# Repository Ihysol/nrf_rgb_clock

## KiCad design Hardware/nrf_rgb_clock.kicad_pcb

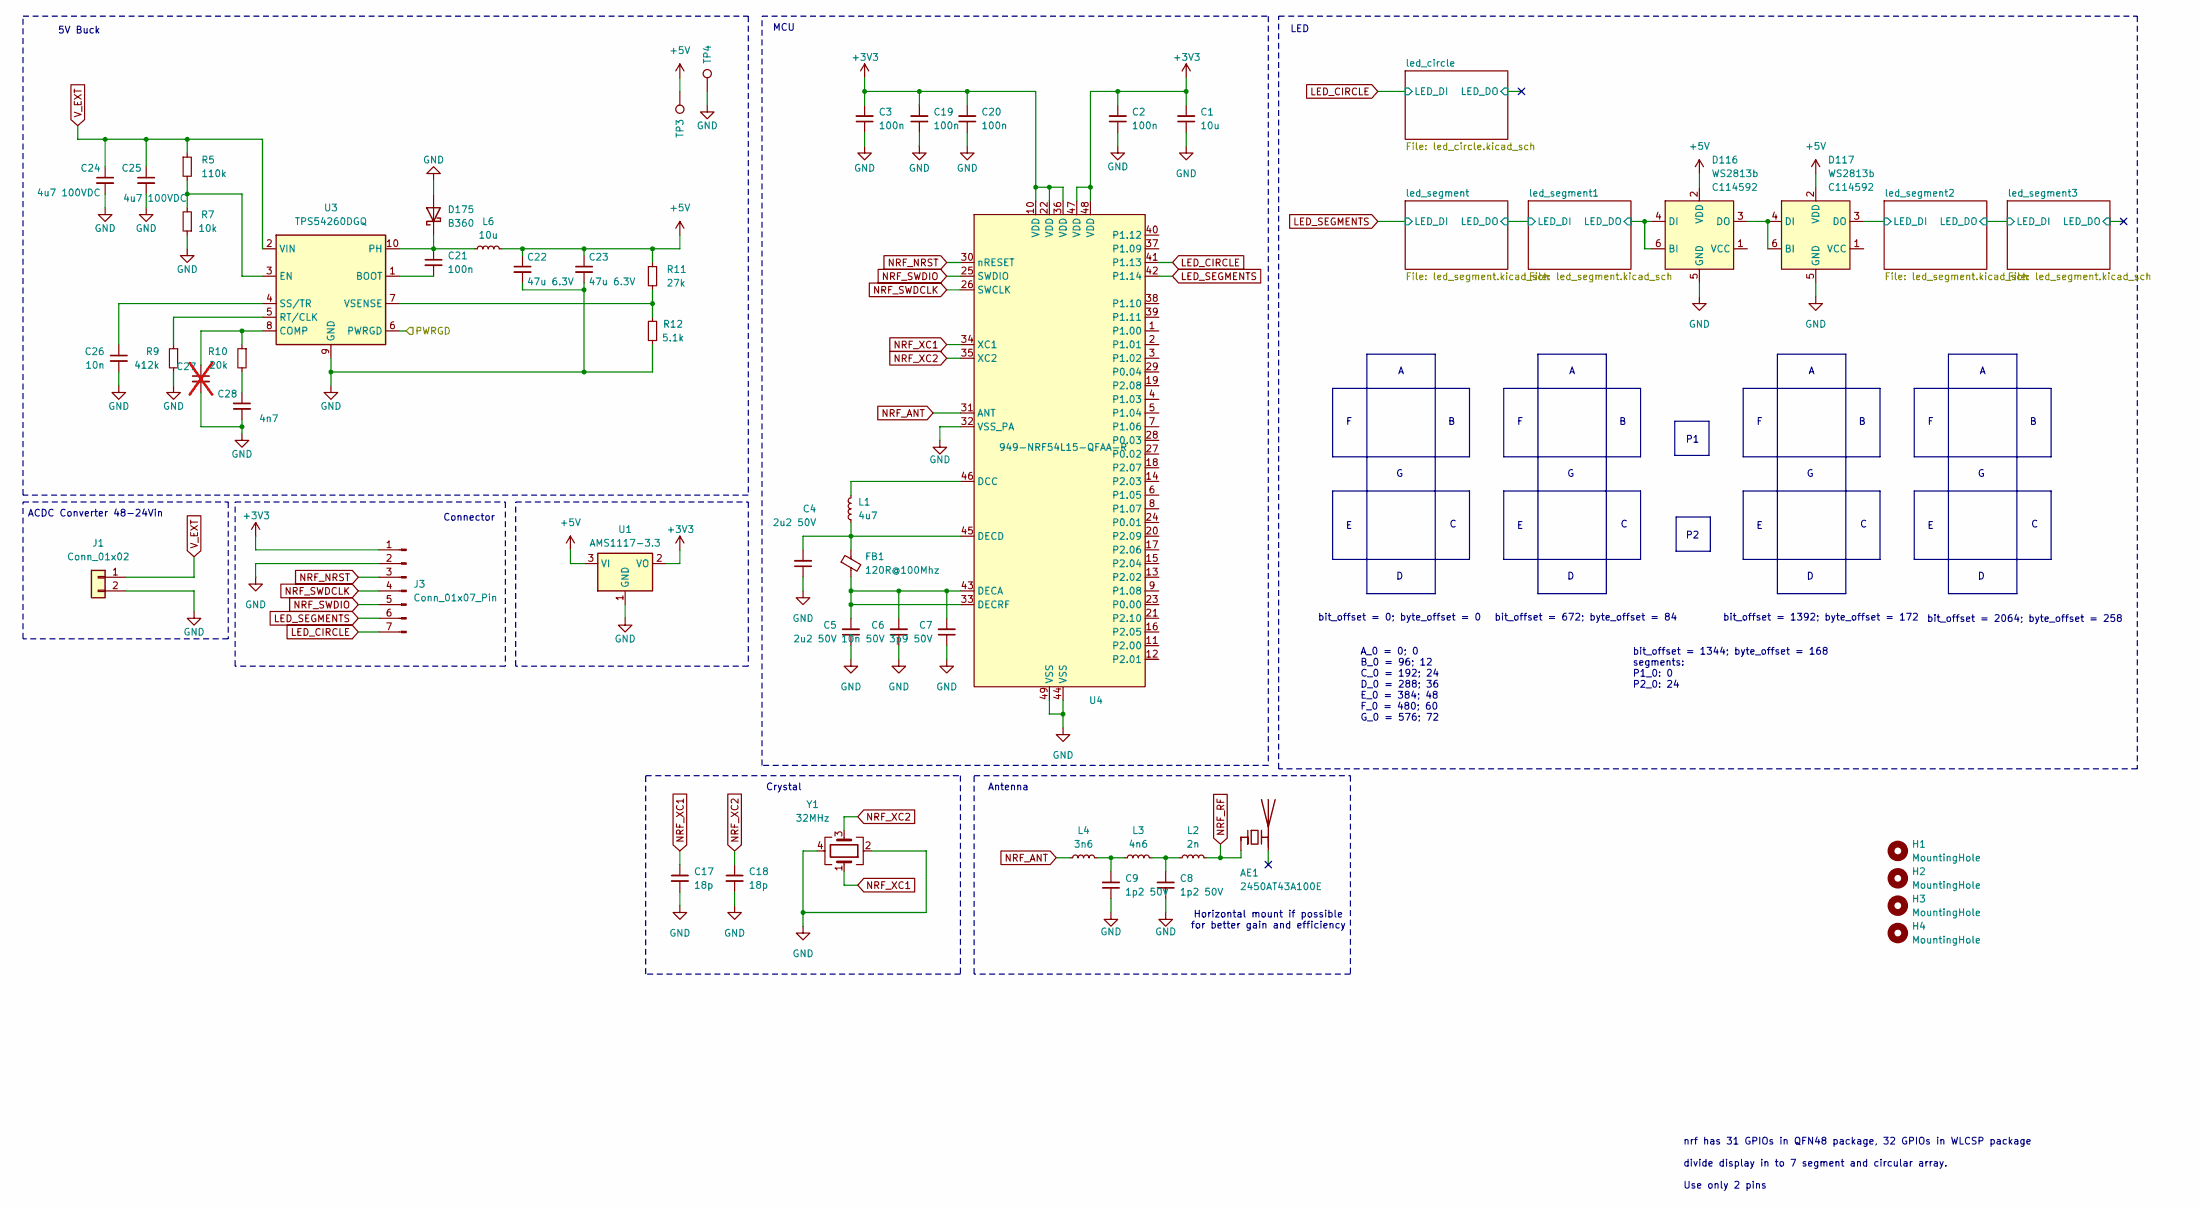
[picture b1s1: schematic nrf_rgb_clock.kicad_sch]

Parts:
AE1: 2450AT43A100E; 2450AT18A100; LCSC C89334
C1: 10u; C_0805_2012Metric; LCSC C2932476
C2, C3, C19, C20: 100n; C_0402_1005Metric; LCSC C696907
C4, C5: 2u2 50V; C_0603_1608Metric; LCSC C7432769
C6: 10n 50V; C_0201_0603Metric; LCSC C5142551
C7: 3p9 50V; C_0201_0603Metric; LCSC C22374845
C8, C9: 1p2 50V; C_0201_0603Metric; LCSC C22374839
C17, C18: 18p; C_0201_0603Metric; LCSC C161409
C21: 100n; C_0402_1005Metric; LCSC C1525
C22, C23: 47u 6.3V; C_0805_2012Metric; LCSC C1710
C24, C25: 4u7 100VDC; C_1206_3216Metric; LCSC C29823
C26: 10n; C_0402_1005Metric; LCSC C15195
C27: C_0603_1608Metric; not fitted
C28: 4n7; C_0603_1608Metric; LCSC C1588
D116, D117: WS2813b; LED_WS2812_PLCC6_5.0x5.0mm_P1.6mm; LCSC C114592
D175: B360; D_SMC; lcsc C12632
FB1: 120R@100Mhz; R_0402_1005Metric; LCSC C337874
H1, H2, H3, H4: MountingHole; MountingHole_3.2mm_M3
J1: Conn_01x02; SHDR4W113P700X508_2X2_1039X1200X1200P; LCSC C8269
J3: Conn_01x07_Pin; PinHeader_1x07_P2.54mm_Vertical
L1: 4u7; LED_0402_1005Metric; LCSC C18221128
L2: 2n; LED_0201_0603Metric; LCSC C412057
L3: 4n6; L_0201_0603Metric; LCSC C108240
L4: 3n6; L_0201_0603Metric; LCSC C237447
L6: 10u; NRS5040T3R3NMGJV; LCSC C223066
R5: 110k; R_0805_2012Metric; LCSC C149504
R7: 10k; R_0402_1005Metric; LCSC C25744
R9: 412k; R_0805_2012Metric; LCSC C22375107
R10: 20k; R_0805_2012Metric; LCSC C4328
R11: 27k; R_0805_2012Metric; LCSC C2907247
R12: 5.1k; R_0402_1005Metric; LCSC C105872
TP3, TP4: TestPoint; TestPoint_THTPad_2.0x2.0mm_Drill1.0mm
U1: AMS1117-3.3; SOT-223-3_TabPin2; lcsc C2891839
U3: TPS54260DGQ; MSOP-10-1EP_3x3mm_P0.5mm_EP2.2x3.1mm_Mask1.83x1.89mm_Therma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; LCSC C51800
U4: QFN-48_EP_6x6_Pitch0.4mm; LCSC C42458750
Y1: 32MHz; Crystal_SMD_3225-4Pin_3.2x2.5mm; LCSC C9009

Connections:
+3V3: C1.2, C2.2, C3.2, C19.2, C20.2, J3.1, U1.2 (VO), U4.10 (VDD), U4.22 (VDD), U4.36 (VDD), U4.47 (VDD), U4.48 (VDD)
+5V: C22.1, C23.1, D116.2 (VDD), D117.2 (VDD), L6.2, R11.1, TP3.1, U1.3 (VI); also elsewhere on the board
/PWRGD: U3.6 (PWRGD)
/led_segment1/LED_DO: D116.4 (DI), D116.6 (BI); also elsewhere on the board
/led_segment2/LED_DI: D117.3 (DO); also elsewhere on the board
GND: C1.1, C2.1, C3.1, C4.1, C5.1, C6.1, C7.1, C8.1, C9.1, C17.2, C18.2, C19.1, C20.1, C22.2, C23.2, C24.2, C25.2, C26.2, C27.2, C28.2, D116.5 (GND), D117.5 (GND), D175.2 (A), J1.2, J3.2, R7.1, R9.2, R12.1, TP4.1, U1.1 (GND), U3.9 (GND), U3.11 (EP), U4.32 (VSS_PA), U4.44 (VSS), U4.49 (VSS), Y1.2, Y1.4; also elsewhere on the board
LED_CIRCLE: J3.7, U4.41 (P1.13); also elsewhere on the board
LED_SEGMENTS: J3.6, U4.42 (P1.14); also elsewhere on the board
NRF_ANT: L4.1, U4.31 (ANT)
NRF_NRST: J3.3, U4.30 (nRESET)
NRF_RF: AE1.1 (FEED), L2.2
NRF_SWDCLK: J3.4, U4.26 (SWCLK)
NRF_SWDIO: J3.5, U4.25 (SWDIO)
NRF_XC1: C17.1, U4.34 (XC1), Y1.1
NRF_XC2: C18.1, U4.35 (XC2), Y1.3
unnamed: C8.2, L2.1, L3.2
unnamed: C9.2, L3.1, L4.2
unnamed: C28.1, R10.2
unnamed: D116.3 (DO), D117.4 (DI), D117.6 (BI)
unnamed: C21.1, D175.1 (K), L6.1, U3.10 (PH)
unnamed: C21.2, U3.1 (BOOT)
unnamed: C27.1, R10.1, U3.8 (COMP)
unnamed: R5.2, R7.2, U3.3 (EN)
unnamed: R9.1, U3.5 (RT/CLK)
unnamed: C26.1, U3.4 (SS/TR)
unnamed: R11.2, R12.2, U3.7 (VSENSE)
unnamed: L1.1, U4.46 (DCC)
unnamed: C5.2, C6.2, C7.2, FB1.2, U4.33 (DECRF), U4.43 (DECA)
unnamed: C4.2, FB1.1, L1.2, U4.45 (DECD)
V_EXT: C24.1, C25.1, J1.1, R5.1, U3.2 (VIN)

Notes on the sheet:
bit_offset = 1344; byte_offset = 168 segments: P1_0: 0 P2_0: 24
ACDC Converter 48-24Vin
Horizontal mount if possible for better gain and efficiency
LED
MCU
bit_offset = 1392; byte_offset = 172
Crystal
5V Buck
bit_offset = 672; byte_offset = 84
nrf has 31 GPIOs in QFN48 package, 32 GPIOs in WLCSP package divide display in to 7 segment and circular array. Use only 2 pins
bit_offset = 0; byte_offset = 0
Connector
Antenna
bit_offset = 2064; byte_offset = 258
A_0 = 0; 0 B_0 = 96; 12 C_0 = 192; 24 D_0 = 288; 36 E_0 = 384; 48 F_0 = 480; 60 G_0 = 576; 72

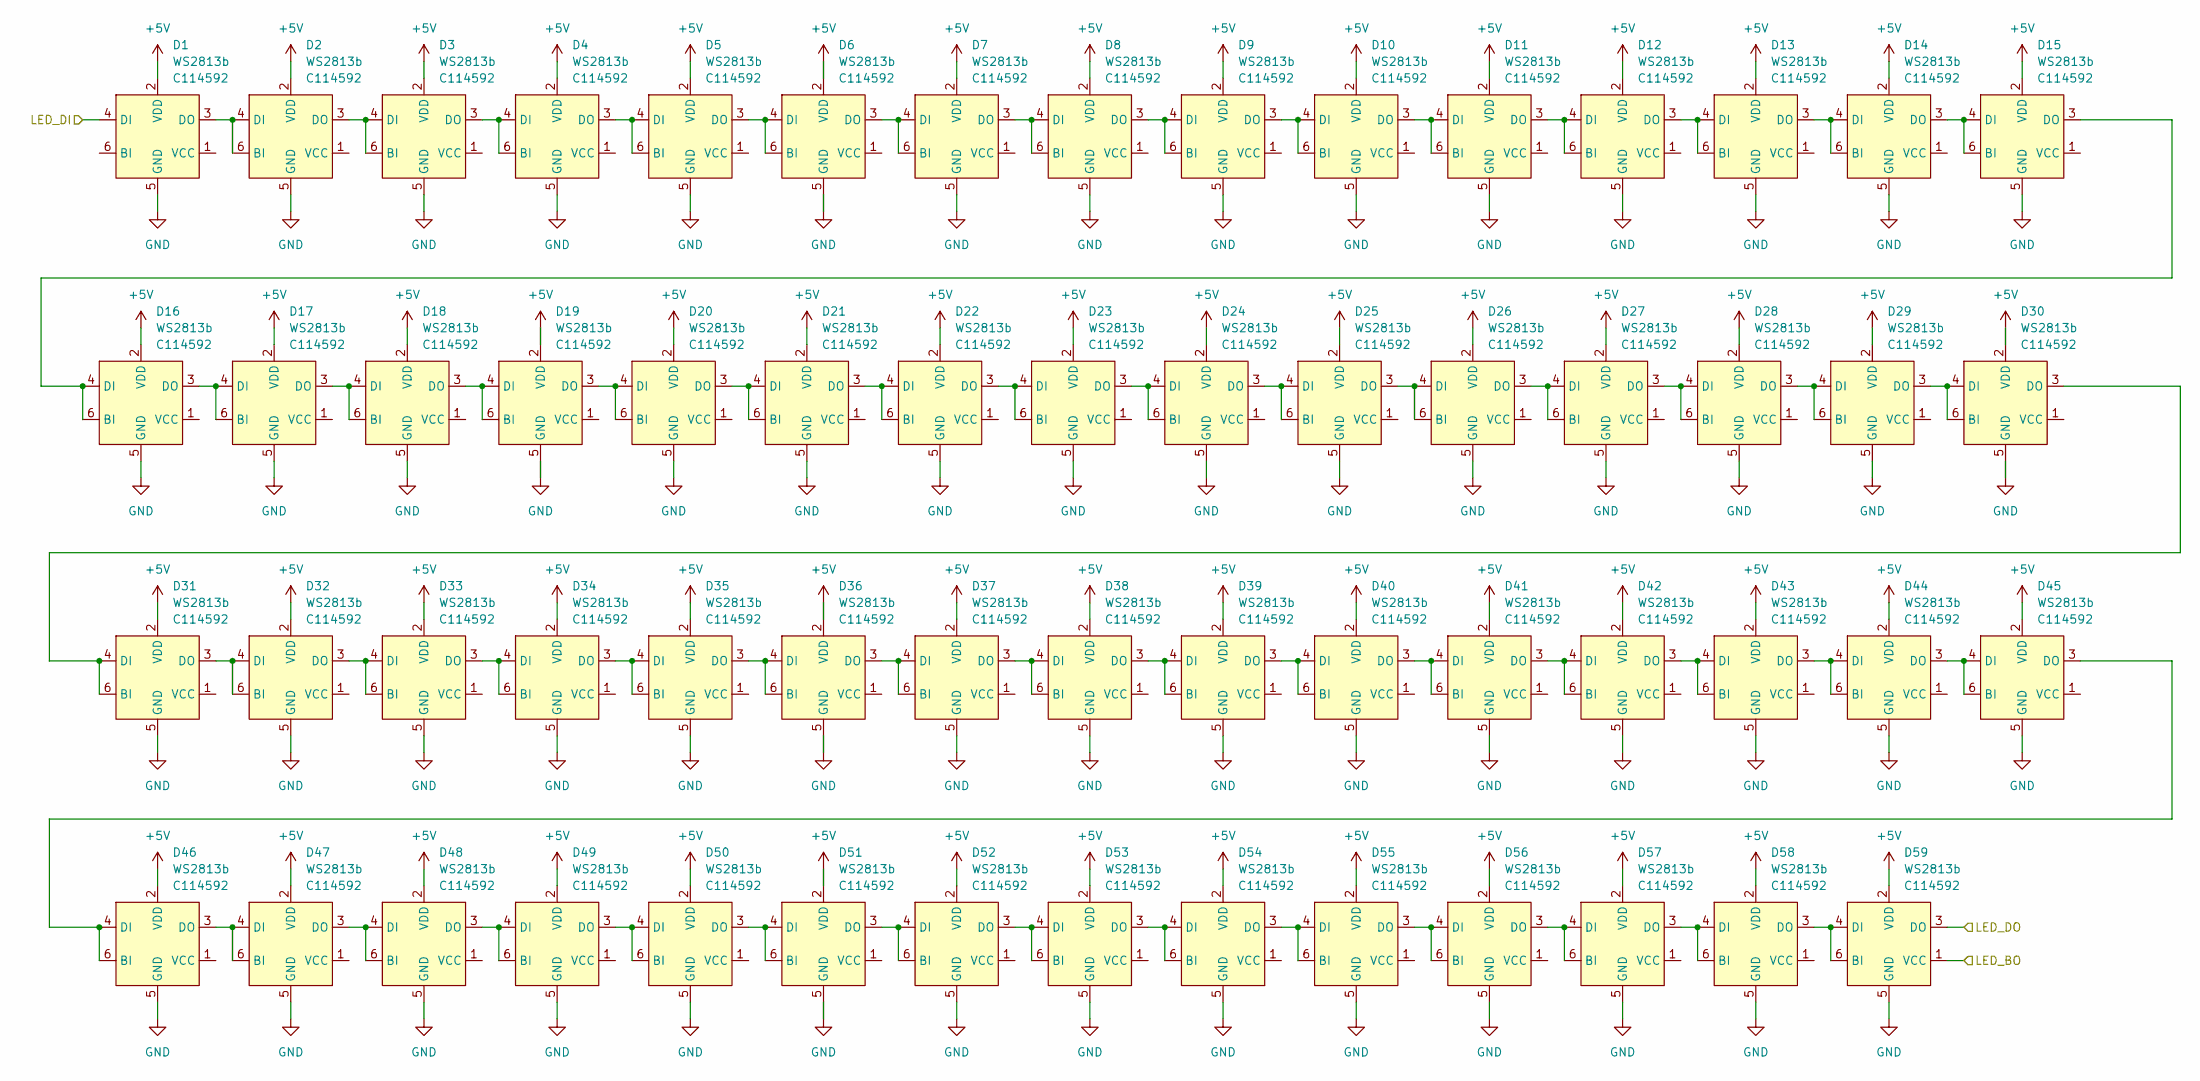
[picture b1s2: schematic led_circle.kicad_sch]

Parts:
D1, D2, D3, D4, D5, D6, D7, D8, D9, D10, D11, D12, D13, D14, D15, D16, D17, D18, D19, D20, D21, D22, D23, D24, D25, D26, D27, D28, D29, D30, D31, D32, D33, D34, D35, D36, D37, D38, D39, D40, D41, D42, D43, D44, D45, D46, D47, D48, D49, D50, D51, D52, D53, D54, D55, D56, D57, D58, D59: WS2813b; LED_WS2812_PLCC6_5.0x5.0mm_P1.6mm; LCSC C114592

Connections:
+5V: D1.2 (VDD), D2.2 (VDD), D3.2 (VDD), D4.2 (VDD), D5.2 (VDD), D6.2 (VDD), D7.2 (VDD), D8.2 (VDD), D9.2 (VDD), D10.2 (VDD), D11.2 (VDD), D12.2 (VDD), D13.2 (VDD), D14.2 (VDD), D15.2 (VDD), D16.2 (VDD), D17.2 (VDD), D18.2 (VDD), D19.2 (VDD), D20.2 (VDD), D21.2 (VDD), D22.2 (VDD), D23.2 (VDD), D24.2 (VDD), D25.2 (VDD), D26.2 (VDD), D27.2 (VDD), D28.2 (VDD), D29.2 (VDD), D30.2 (VDD), D31.2 (VDD), D32.2 (VDD), D33.2 (VDD), D34.2 (VDD), D35.2 (VDD), D36.2 (VDD), D37.2 (VDD), D38.2 (VDD), D39.2 (VDD), D40.2 (VDD), D41.2 (VDD), D42.2 (VDD), D43.2 (VDD), D44.2 (VDD), D45.2 (VDD), D46.2 (VDD), D47.2 (VDD), D48.2 (VDD), D49.2 (VDD), D50.2 (VDD), D51.2 (VDD), D52.2 (VDD), D53.2 (VDD), D54.2 (VDD), D55.2 (VDD), D56.2 (VDD), D57.2 (VDD), D58.2 (VDD), D59.2 (VDD); also elsewhere on the board
/led_circle/LED_BO: D59.1 (VCC)
/led_circle/LED_DO: D59.3 (DO)
GND: D1.5 (GND), D2.5 (GND), D3.5 (GND), D4.5 (GND), D5.5 (GND), D6.5 (GND), D7.5 (GND), D8.5 (GND), D9.5 (GND), D10.5 (GND), D11.5 (GND), D12.5 (GND), D13.5 (GND), D14.5 (GND), D15.5 (GND), D16.5 (GND), D17.5 (GND), D18.5 (GND), D19.5 (GND), D20.5 (GND), D21.5 (GND), D22.5 (GND), D23.5 (GND), D24.5 (GND), D25.5 (GND), D26.5 (GND), D27.5 (GND), D28.5 (GND), D29.5 (GND), D30.5 (GND), D31.5 (GND), D32.5 (GND), D33.5 (GND), D34.5 (GND), D35.5 (GND), D36.5 (GND), D37.5 (GND), D38.5 (GND), D39.5 (GND), D40.5 (GND), D41.5 (GND), D42.5 (GND), D43.5 (GND), D44.5 (GND), D45.5 (GND), D46.5 (GND), D47.5 (GND), D48.5 (GND), D49.5 (GND), D50.5 (GND), D51.5 (GND), D52.5 (GND), D53.5 (GND), D54.5 (GND), D55.5 (GND), D56.5 (GND), D57.5 (GND), D58.5 (GND), D59.5 (GND); also elsewhere on the board
LED_CIRCLE: D1.4 (DI); also elsewhere on the board
unnamed: D1.3 (DO), D2.4 (DI), D2.6 (BI)
unnamed: D2.3 (DO), D3.4 (DI), D3.6 (BI)
unnamed: D3.3 (DO), D4.4 (DI), D4.6 (BI)
unnamed: D4.3 (DO), D5.4 (DI), D5.6 (BI)
unnamed: D5.3 (DO), D6.4 (DI), D6.6 (BI)
unnamed: D6.3 (DO), D7.4 (DI), D7.6 (BI)
unnamed: D7.3 (DO), D8.4 (DI), D8.6 (BI)
unnamed: D8.3 (DO), D9.4 (DI), D9.6 (BI)
unnamed: D9.3 (DO), D10.4 (DI), D10.6 (BI)
unnamed: D10.3 (DO), D11.4 (DI), D11.6 (BI)
unnamed: D11.3 (DO), D12.4 (DI), D12.6 (BI)
unnamed: D12.3 (DO), D13.4 (DI), D13.6 (BI)
unnamed: D13.3 (DO), D14.4 (DI), D14.6 (BI)
unnamed: D14.3 (DO), D15.4 (DI), D15.6 (BI)
unnamed: D15.3 (DO), D16.4 (DI), D16.6 (BI)
unnamed: D16.3 (DO), D17.4 (DI), D17.6 (BI)
unnamed: D17.3 (DO), D18.4 (DI), D18.6 (BI)
unnamed: D18.3 (DO), D19.4 (DI), D19.6 (BI)
unnamed: D19.3 (DO), D20.4 (DI), D20.6 (BI)
unnamed: D20.3 (DO), D21.4 (DI), D21.6 (BI)
unnamed: D21.3 (DO), D22.4 (DI), D22.6 (BI)
unnamed: D22.3 (DO), D23.4 (DI), D23.6 (BI)
unnamed: D23.3 (DO), D24.4 (DI), D24.6 (BI)
unnamed: D24.3 (DO), D25.4 (DI), D25.6 (BI)
unnamed: D25.3 (DO), D26.4 (DI), D26.6 (BI)
unnamed: D26.3 (DO), D27.4 (DI), D27.6 (BI)
unnamed: D27.3 (DO), D28.4 (DI), D28.6 (BI)
unnamed: D28.3 (DO), D29.4 (DI), D29.6 (BI)
unnamed: D29.3 (DO), D30.4 (DI), D30.6 (BI)
unnamed: D30.3 (DO), D31.4 (DI), D31.6 (BI)
unnamed: D31.3 (DO), D32.4 (DI), D32.6 (BI)
unnamed: D32.3 (DO), D33.4 (DI), D33.6 (BI)
unnamed: D33.3 (DO), D34.4 (DI), D34.6 (BI)
unnamed: D34.3 (DO), D35.4 (DI), D35.6 (BI)
unnamed: D35.3 (DO), D36.4 (DI), D36.6 (BI)
unnamed: D36.3 (DO), D37.4 (DI), D37.6 (BI)
unnamed: D37.3 (DO), D38.4 (DI), D38.6 (BI)
unnamed: D38.3 (DO), D39.4 (DI), D39.6 (BI)
unnamed: D39.3 (DO), D40.4 (DI), D40.6 (BI)
unnamed: D40.3 (DO), D41.4 (DI), D41.6 (BI)
unnamed: D41.3 (DO), D42.4 (DI), D42.6 (BI)
unnamed: D42.3 (DO), D43.4 (DI), D43.6 (BI)
unnamed: D43.3 (DO), D44.4 (DI), D44.6 (BI)
unnamed: D44.3 (DO), D45.4 (DI), D45.6 (BI)
unnamed: D45.3 (DO), D46.4 (DI), D46.6 (BI)
unnamed: D46.3 (DO), D47.4 (DI), D47.6 (BI)
unnamed: D47.3 (DO), D48.4 (DI), D48.6 (BI)
unnamed: D48.3 (DO), D49.4 (DI), D49.6 (BI)
unnamed: D49.3 (DO), D50.4 (DI), D50.6 (BI)
unnamed: D50.3 (DO), D51.4 (DI), D51.6 (BI)
unnamed: D51.3 (DO), D52.4 (DI), D52.6 (BI)
unnamed: D52.3 (DO), D53.4 (DI), D53.6 (BI)
unnamed: D53.3 (DO), D54.4 (DI), D54.6 (BI)
unnamed: D54.3 (DO), D55.4 (DI), D55.6 (BI)
unnamed: D55.3 (DO), D56.4 (DI), D56.6 (BI)
unnamed: D56.3 (DO), D57.4 (DI), D57.6 (BI)
unnamed: D57.3 (DO), D58.4 (DI), D58.6 (BI)
unnamed: D58.3 (DO), D59.4 (DI), D59.6 (BI)

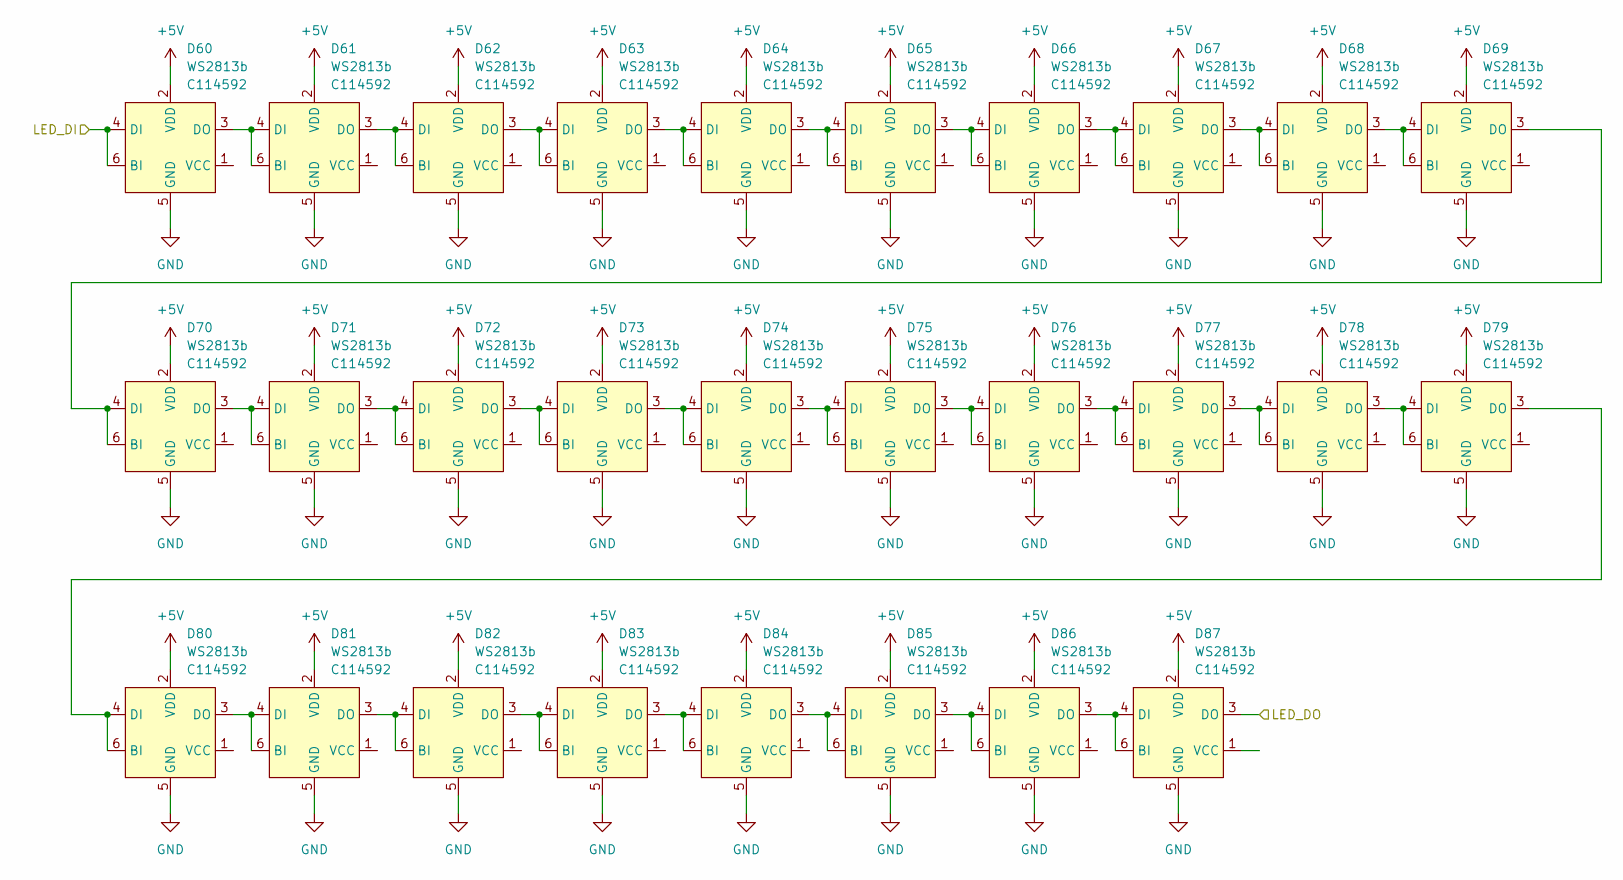
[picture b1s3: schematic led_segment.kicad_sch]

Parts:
D60, D61, D62, D63, D64, D65, D66, D67, D68, D69, D70, D71, D72, D73, D74, D75, D76, D77, D78, D79, D80, D81, D82, D83, D84, D85, D86, D87: WS2813b; LED_WS2812_PLCC6_5.0x5.0mm_P1.6mm; LCSC C114592

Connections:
+5V: D60.2 (VDD), D61.2 (VDD), D62.2 (VDD), D63.2 (VDD), D64.2 (VDD), D65.2 (VDD), D66.2 (VDD), D67.2 (VDD), D68.2 (VDD), D69.2 (VDD), D70.2 (VDD), D71.2 (VDD), D72.2 (VDD), D73.2 (VDD), D74.2 (VDD), D75.2 (VDD), D76.2 (VDD), D77.2 (VDD), D78.2 (VDD), D79.2 (VDD), D80.2 (VDD), D81.2 (VDD), D82.2 (VDD), D83.2 (VDD), D84.2 (VDD), D85.2 (VDD), D86.2 (VDD), D87.2 (VDD); also elsewhere on the board
/led_segment/LED_DO: D87.3 (DO); also elsewhere on the board
GND: D60.5 (GND), D61.5 (GND), D62.5 (GND), D63.5 (GND), D64.5 (GND), D65.5 (GND), D66.5 (GND), D67.5 (GND), D68.5 (GND), D69.5 (GND), D70.5 (GND), D71.5 (GND), D72.5 (GND), D73.5 (GND), D74.5 (GND), D75.5 (GND), D76.5 (GND), D77.5 (GND), D78.5 (GND), D79.5 (GND), D80.5 (GND), D81.5 (GND), D82.5 (GND), D83.5 (GND), D84.5 (GND), D85.5 (GND), D86.5 (GND), D87.5 (GND); also elsewhere on the board
LED_SEGMENTS: D60.4 (DI), D60.6 (BI); also elsewhere on the board
unnamed: D60.3 (DO), D61.4 (DI), D61.6 (BI)
unnamed: D61.3 (DO), D62.4 (DI), D62.6 (BI)
unnamed: D62.3 (DO), D63.4 (DI), D63.6 (BI)
unnamed: D63.3 (DO), D64.4 (DI), D64.6 (BI)
unnamed: D64.3 (DO), D65.4 (DI), D65.6 (BI)
unnamed: D65.3 (DO), D66.4 (DI), D66.6 (BI)
unnamed: D66.3 (DO), D67.4 (DI), D67.6 (BI)
unnamed: D67.3 (DO), D68.4 (DI), D68.6 (BI)
unnamed: D68.3 (DO), D69.4 (DI), D69.6 (BI)
unnamed: D69.3 (DO), D70.4 (DI), D70.6 (BI)
unnamed: D70.3 (DO), D71.4 (DI), D71.6 (BI)
unnamed: D71.3 (DO), D72.4 (DI), D72.6 (BI)
unnamed: D72.3 (DO), D73.4 (DI), D73.6 (BI)
unnamed: D73.3 (DO), D74.4 (DI), D74.6 (BI)
unnamed: D74.3 (DO), D75.4 (DI), D75.6 (BI)
unnamed: D75.3 (DO), D76.4 (DI), D76.6 (BI)
unnamed: D76.3 (DO), D77.4 (DI), D77.6 (BI)
unnamed: D77.3 (DO), D78.4 (DI), D78.6 (BI)
unnamed: D78.3 (DO), D79.4 (DI), D79.6 (BI)
unnamed: D79.3 (DO), D80.4 (DI), D80.6 (BI)
unnamed: D80.3 (DO), D81.4 (DI), D81.6 (BI)
unnamed: D81.3 (DO), D82.4 (DI), D82.6 (BI)
unnamed: D82.3 (DO), D83.4 (DI), D83.6 (BI)
unnamed: D83.3 (DO), D84.4 (DI), D84.6 (BI)
unnamed: D84.3 (DO), D85.4 (DI), D85.6 (BI)
unnamed: D85.3 (DO), D86.4 (DI), D86.6 (BI)
unnamed: D86.3 (DO), D87.4 (DI), D87.6 (BI)

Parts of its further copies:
D88, D89, D90, D91, D92, D93, D94, D95, D96, D97, D98, D99, D100, D101, D102, D103, D104, D105, D106, D107, D108, D109, D110, D111, D112, D113, D114, D115, D118, D119, D120, D121, D122, D123, D124, D125, D126, D127, D128, D129, D130, D131, D132, D133, D134, D135, D136, D137, D138, D139, D140, D141, D142, D143, D144, D145, D146, D147, D148, D149, D150, D151, D152, D153, D154, D155, D156, D157, D158, D159, D160, D161, D162, D163, D164, D165, D166, D167, D168, D169, D170, D171, D172, D173: WS2813b; LED_WS2812_PLCC6_5.0x5.0mm_P1.6mm; LCSC C114592

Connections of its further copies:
+5V: D88.2 (VDD), D89.2 (VDD), D90.2 (VDD), D91.2 (VDD), D92.2 (VDD), D93.2 (VDD), D94.2 (VDD), D95.2 (VDD), D96.2 (VDD), D97.2 (VDD), D98.2 (VDD), D99.2 (VDD), D100.2 (VDD), D101.2 (VDD), D102.2 (VDD), D103.2 (VDD), D104.2 (VDD), D105.2 (VDD), D106.2 (VDD), D107.2 (VDD), D108.2 (VDD), D109.2 (VDD), D110.2 (VDD), D111.2 (VDD), D112.2 (VDD), D113.2 (VDD), D114.2 (VDD), D115.2 (VDD), D118.2 (VDD), D119.2 (VDD), D120.2 (VDD), D121.2 (VDD), D122.2 (VDD), D123.2 (VDD), D124.2 (VDD), D125.2 (VDD), D126.2 (VDD), D127.2 (VDD), D128.2 (VDD), D129.2 (VDD), D130.2 (VDD), D131.2 (VDD), D132.2 (VDD), D133.2 (VDD), D134.2 (VDD), D135.2 (VDD), D136.2 (VDD), D137.2 (VDD), D138.2 (VDD), D139.2 (VDD), D140.2 (VDD), D141.2 (VDD), D142.2 (VDD), D143.2 (VDD), D144.2 (VDD), D145.2 (VDD), D146.2 (VDD), D147.2 (VDD), D148.2 (VDD), D149.2 (VDD), D150.2 (VDD), D151.2 (VDD), D152.2 (VDD), D153.2 (VDD), D154.2 (VDD), D155.2 (VDD), D156.2 (VDD), D157.2 (VDD), D158.2 (VDD), D159.2 (VDD), D160.2 (VDD), D161.2 (VDD), D162.2 (VDD), D163.2 (VDD), D164.2 (VDD), D165.2 (VDD), D166.2 (VDD), D167.2 (VDD), D168.2 (VDD), D169.2 (VDD), D170.2 (VDD), D171.2 (VDD), D172.2 (VDD), D173.2 (VDD); also elsewhere on the board
/led_segment1/LED_DO: D115.3 (DO); also elsewhere on the board
/led_segment2/LED_DI: D118.4 (DI), D118.6 (BI); also elsewhere on the board
/led_segment2/LED_DO: D145.3 (DO), D146.4 (DI), D146.6 (BI)
/led_segment3/LED_DO: D173.3 (DO)
/led_segment/LED_DO: D88.4 (DI), D88.6 (BI); also elsewhere on the board
GND: D88.5 (GND), D89.5 (GND), D90.5 (GND), D91.5 (GND), D92.5 (GND), D93.5 (GND), D94.5 (GND), D95.5 (GND), D96.5 (GND), D97.5 (GND), D98.5 (GND), D99.5 (GND), D100.5 (GND), D101.5 (GND), D102.5 (GND), D103.5 (GND), D104.5 (GND), D105.5 (GND), D106.5 (GND), D107.5 (GND), D108.5 (GND), D109.5 (GND), D110.5 (GND), D111.5 (GND), D112.5 (GND), D113.5 (GND), D114.5 (GND), D115.5 (GND), D118.5 (GND), D119.5 (GND), D120.5 (GND), D121.5 (GND), D122.5 (GND), D123.5 (GND), D124.5 (GND), D125.5 (GND), D126.5 (GND), D127.5 (GND), D128.5 (GND), D129.5 (GND), D130.5 (GND), D131.5 (GND), D132.5 (GND), D133.5 (GND), D134.5 (GND), D135.5 (GND), D136.5 (GND), D137.5 (GND), D138.5 (GND), D139.5 (GND), D140.5 (GND), D141.5 (GND), D142.5 (GND), D143.5 (GND), D144.5 (GND), D145.5 (GND), D146.5 (GND), D147.5 (GND), D148.5 (GND), D149.5 (GND), D150.5 (GND), D151.5 (GND), D152.5 (GND), D153.5 (GND), D154.5 (GND), D155.5 (GND), D156.5 (GND), D157.5 (GND), D158.5 (GND), D159.5 (GND), D160.5 (GND), D161.5 (GND), D162.5 (GND), D163.5 (GND), D164.5 (GND), D165.5 (GND), D166.5 (GND), D167.5 (GND), D168.5 (GND), D169.5 (GND), D170.5 (GND), D171.5 (GND), D172.5 (GND), D173.5 (GND); also elsewhere on the board
unnamed: D88.3 (DO), D89.4 (DI), D89.6 (BI)
unnamed: D89.3 (DO), D90.4 (DI), D90.6 (BI)
unnamed: D90.3 (DO), D91.4 (DI), D91.6 (BI)
unnamed: D91.3 (DO), D92.4 (DI), D92.6 (BI)
unnamed: D92.3 (DO), D93.4 (DI), D93.6 (BI)
unnamed: D93.3 (DO), D94.4 (DI), D94.6 (BI)
unnamed: D94.3 (DO), D95.4 (DI), D95.6 (BI)
unnamed: D95.3 (DO), D96.4 (DI), D96.6 (BI)
unnamed: D96.3 (DO), D97.4 (DI), D97.6 (BI)
unnamed: D97.3 (DO), D98.4 (DI), D98.6 (BI)
unnamed: D98.3 (DO), D99.4 (DI), D99.6 (BI)
unnamed: D99.3 (DO), D100.4 (DI), D100.6 (BI)
unnamed: D100.3 (DO), D101.4 (DI), D101.6 (BI)
unnamed: D101.3 (DO), D102.4 (DI), D102.6 (BI)
unnamed: D102.3 (DO), D103.4 (DI), D103.6 (BI)
unnamed: D103.3 (DO), D104.4 (DI), D104.6 (BI)
unnamed: D104.3 (DO), D105.4 (DI), D105.6 (BI)
unnamed: D105.3 (DO), D106.4 (DI), D106.6 (BI)
unnamed: D106.3 (DO), D107.4 (DI), D107.6 (BI)
unnamed: D107.3 (DO), D108.4 (DI), D108.6 (BI)
unnamed: D108.3 (DO), D109.4 (DI), D109.6 (BI)
unnamed: D109.3 (DO), D110.4 (DI), D110.6 (BI)
unnamed: D110.3 (DO), D111.4 (DI), D111.6 (BI)
unnamed: D111.3 (DO), D112.4 (DI), D112.6 (BI)
unnamed: D112.3 (DO), D113.4 (DI), D113.6 (BI)
unnamed: D113.3 (DO), D114.4 (DI), D114.6 (BI)
unnamed: D114.3 (DO), D115.4 (DI), D115.6 (BI)
unnamed: D118.3 (DO), D119.4 (DI), D119.6 (BI)
unnamed: D119.3 (DO), D120.4 (DI), D120.6 (BI)
unnamed: D120.3 (DO), D121.4 (DI), D121.6 (BI)
unnamed: D121.3 (DO), D122.4 (DI), D122.6 (BI)
unnamed: D122.3 (DO), D123.4 (DI), D123.6 (BI)
unnamed: D123.3 (DO), D124.4 (DI), D124.6 (BI)
unnamed: D124.3 (DO), D125.4 (DI), D125.6 (BI)
unnamed: D125.3 (DO), D126.4 (DI), D126.6 (BI)
unnamed: D126.3 (DO), D127.4 (DI), D127.6 (BI)
unnamed: D127.3 (DO), D128.4 (DI), D128.6 (BI)
unnamed: D128.3 (DO), D129.4 (DI), D129.6 (BI)
unnamed: D129.3 (DO), D130.4 (DI), D130.6 (BI)
unnamed: D130.3 (DO), D131.4 (DI), D131.6 (BI)
unnamed: D131.3 (DO), D132.4 (DI), D132.6 (BI)
unnamed: D132.3 (DO), D133.4 (DI), D133.6 (BI)
unnamed: D133.3 (DO), D134.4 (DI), D134.6 (BI)
unnamed: D134.3 (DO), D135.4 (DI), D135.6 (BI)
unnamed: D135.3 (DO), D136.4 (DI), D136.6 (BI)
unnamed: D136.3 (DO), D137.4 (DI), D137.6 (BI)
unnamed: D137.3 (DO), D138.4 (DI), D138.6 (BI)
unnamed: D138.3 (DO), D139.4 (DI), D139.6 (BI)
unnamed: D139.3 (DO), D140.4 (DI), D140.6 (BI)
unnamed: D140.3 (DO), D141.4 (DI), D141.6 (BI)
unnamed: D141.3 (DO), D142.4 (DI), D142.6 (BI)
unnamed: D142.3 (DO), D143.4 (DI), D143.6 (BI)
unnamed: D143.3 (DO), D144.4 (DI), D144.6 (BI)
unnamed: D144.3 (DO), D145.4 (DI), D145.6 (BI)
unnamed: D146.3 (DO), D147.4 (DI), D147.6 (BI)
unnamed: D147.3 (DO), D148.4 (DI), D148.6 (BI)
unnamed: D148.3 (DO), D149.4 (DI), D149.6 (BI)
unnamed: D149.3 (DO), D150.4 (DI), D150.6 (BI)
unnamed: D150.3 (DO), D151.4 (DI), D151.6 (BI)
unnamed: D151.3 (DO), D152.4 (DI), D152.6 (BI)
unnamed: D152.3 (DO), D153.4 (DI), D153.6 (BI)
unnamed: D153.3 (DO), D154.4 (DI), D154.6 (BI)
unnamed: D154.3 (DO), D155.4 (DI), D155.6 (BI)
unnamed: D155.3 (DO), D156.4 (DI), D156.6 (BI)
unnamed: D156.3 (DO), D157.4 (DI), D157.6 (BI)
unnamed: D157.3 (DO), D158.4 (DI), D158.6 (BI)
unnamed: D158.3 (DO), D159.4 (DI), D159.6 (BI)
unnamed: D159.3 (DO), D160.4 (DI), D160.6 (BI)
unnamed: D160.3 (DO), D161.4 (DI), D161.6 (BI)
unnamed: D161.3 (DO), D162.4 (DI), D162.6 (BI)
unnamed: D162.3 (DO), D163.4 (DI), D163.6 (BI)
unnamed: D163.3 (DO), D164.4 (DI), D164.6 (BI)
unnamed: D164.3 (DO), D165.4 (DI), D165.6 (BI)
unnamed: D165.3 (DO), D166.4 (DI), D166.6 (BI)
unnamed: D166.3 (DO), D167.4 (DI), D167.6 (BI)
unnamed: D167.3 (DO), D168.4 (DI), D168.6 (BI)
unnamed: D168.3 (DO), D169.4 (DI), D169.6 (BI)
unnamed: D169.3 (DO), D170.4 (DI), D170.6 (BI)
unnamed: D170.3 (DO), D171.4 (DI), D171.6 (BI)
unnamed: D171.3 (DO), D172.4 (DI), D172.6 (BI)
unnamed: D172.3 (DO), D173.4 (DI), D173.6 (BI)

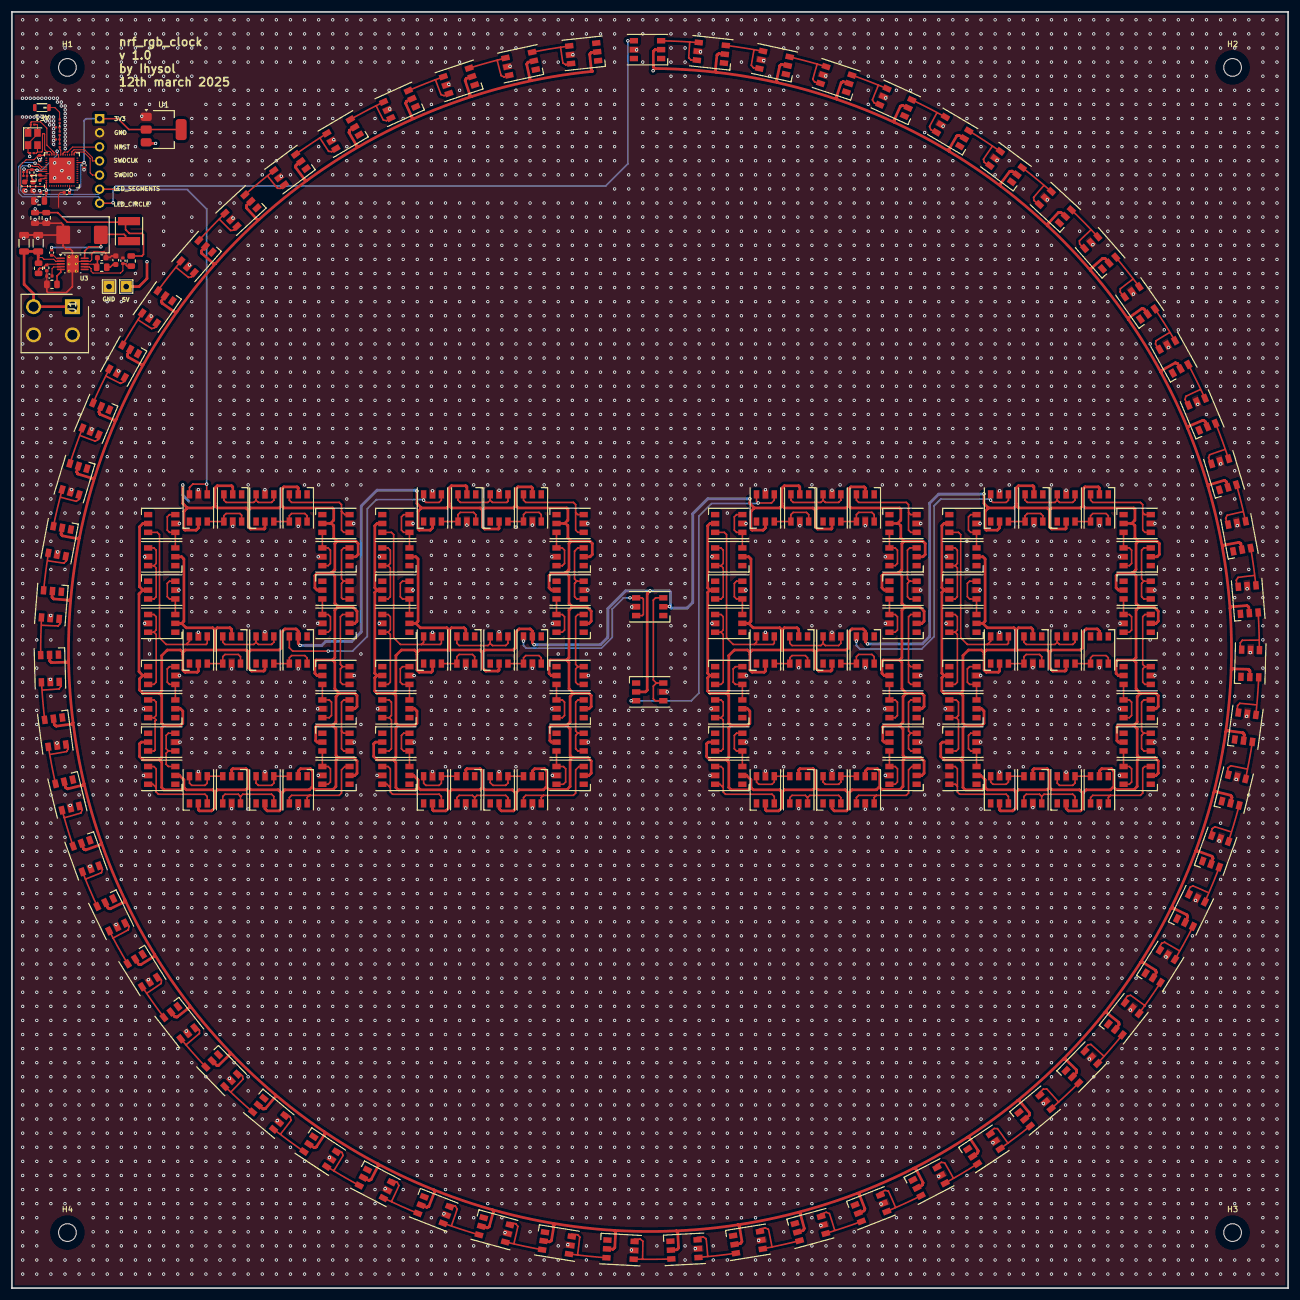
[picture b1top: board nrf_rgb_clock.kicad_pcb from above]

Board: 4 copper layers, 230.0 x 230.0 mm, 220 parts (1 on the bottom side), 197 nets.

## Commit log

2024-12-09 added MFN to nRF54L15-CAAA
2024-12-29 led placement on pcb
2025-01-05 Added bitoffsets and antenna
2025-01-05 added LCSC number and datasheets
2025-01-09 progressed layout
2025-02-14 layout progress
2025-03-11 impedance match 50R + 4 layer
2025-03-12 finalized layout, everything on top + LCSC numbers
2025-03-12 finalized layout, via stitching
2025-03-12 changed antenna
2025-03-12 removed d* reference designators
2025-03-12 finalized layout
2025-04-05 updated lcsc numbers
2025-06-30 Added code with WiFi functionality
2025-06-30 new tps
2025-07-02 sw udpate
2025-07-22 added battery and rtc
2025-07-22 updated gitignore
2025-07-22 updated .gitignore
2025-07-22 added wifi_secrets.h
2025-07-22 moved to millis() implementation. Only check NTP time once on startup
